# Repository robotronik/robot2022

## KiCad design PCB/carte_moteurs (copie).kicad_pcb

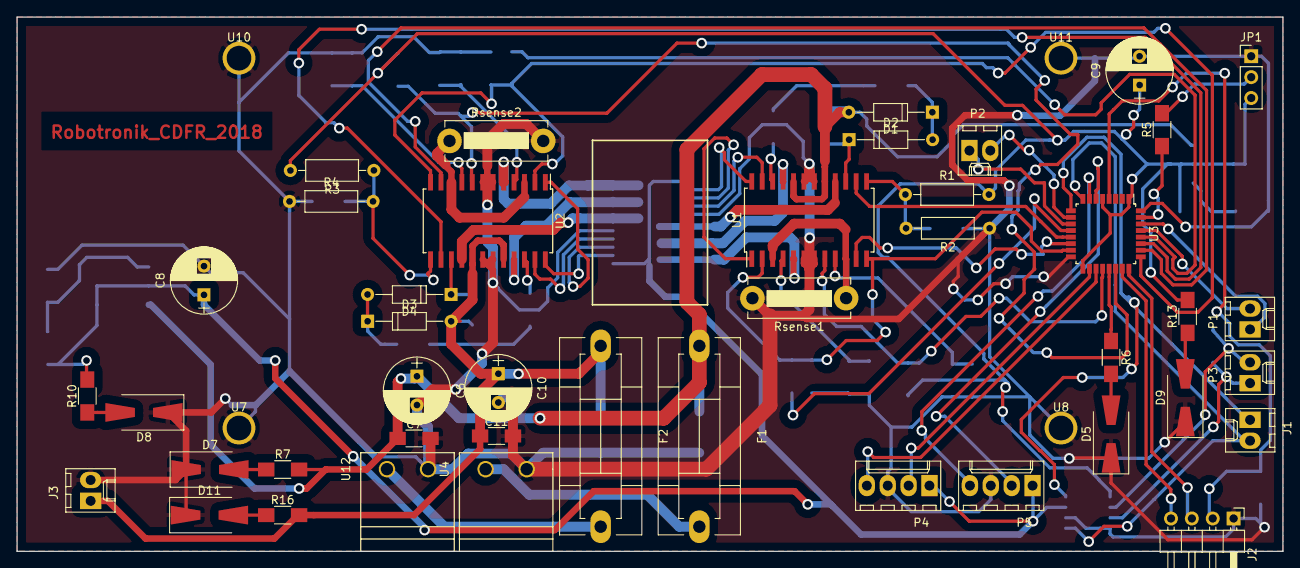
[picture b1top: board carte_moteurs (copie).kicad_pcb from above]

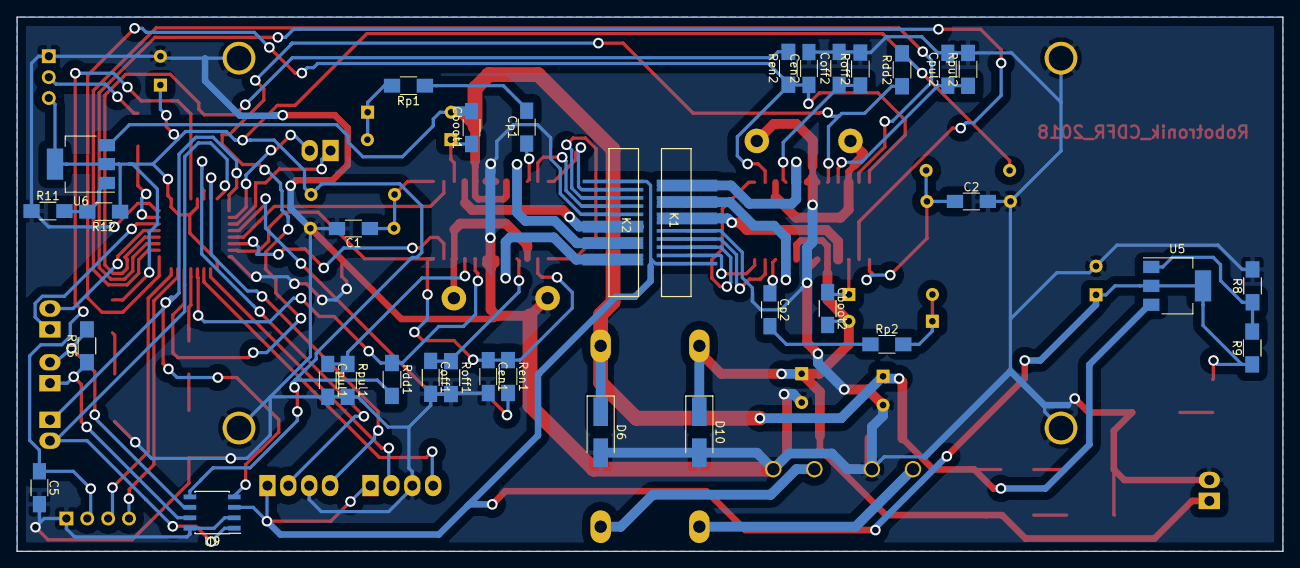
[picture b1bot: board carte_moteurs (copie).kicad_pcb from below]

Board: 2 copper layers, 154.0 x 65.0 mm, 82 parts (35 on the bottom side), 70 nets.

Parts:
C1, C2: C; C_1206_HandSoldering
C5, C7, C11: 100nC; C_1206_HandSoldering
C6, C10: 100uCP; CP_Radial_D8.0mm_P3.50mm
C8, C9: 10uC; CP_Radial_D8.0mm_P3.50mm
Cboot1, Cboot2: 220nC; C_1206_HandSoldering
Cen1, Cen2: 5,6nC; C_1206_HandSoldering
Coff1, Coff2: 1nC; C_1206_HandSoldering
Cp1, Cp2: 10nC; C_1206_HandSoldering
Cpul1, Cpul2: 10nC; C_1206_HandSoldering
D1, D2, D3, D4: 1N4148; D_DO-35_SOD27_P10.16mm_Horizontal
D5, D11: LED_ALT; D_SMA-SMB_Universal_Handsoldering
D6, D10: D_10A; D_SMA_Handsoldering
D7: LED_VCC; D_SMA-SMB_Universal_Handsoldering
D8: LED_5V; D_SMA-SMB_Universal_Handsoldering
D9: LED_3.3V; D_SMA-SMB_Universal_Handsoldering
F1, F2: Fuse; Fuseholder5x20_horiz_SemiClosed_Casing10x25mm
J1: CONN_SERIAL; Molex_KK-6410-02_02x2.54mm_Straight
J2: swdio; Pin_Header_Angled_1x04_Pitch2.54mm
J3: FAN; Molex_KK-6410-02_02x2.54mm_Straight
JP1: Jumper_NC_Dual; Pin_Header_Straight_1x03_Pitch2.54mm
K1, K2: Maxon-200142; Molex-52610-1133
P1: CONN_I2C; Molex_KK-6410-02_02x2.54mm_Straight
P2: CONN_FREE; Molex_KK-6410-02_02x2.54mm_Straight
P3: CONN_CAN; Molex_KK-6410-02_02x2.54mm_Straight
P4: encoder_2; Molex_KK-6410-04_04x2.54mm_Straight
P5: encoder_1; Molex_KK-6410-04_04x2.54mm_Straight
R1, R2, R3, R4: R; R_Axial_DIN0207_L6.3mm_D2.5mm_P10.16mm_Horizontal
R5, R9: 10kR; R_1206_HandSoldering
R6, R7, R10, R13, R15, R16: R; R_1206_HandSoldering
R8: 3.3kR; R_1206_HandSoldering
R11: 33kR; R_1206_HandSoldering
R12: 56kR; R_1206_HandSoldering
Rdd1, Rdd2: 1kR; R_1206_HandSoldering
Ren1, Ren2: 100kR; R_1206_HandSoldering
Roff1, Roff2: 33kR; R_1206_HandSoldering
Rp1, Rp2: 100R; R_1206_HandSoldering
Rpul1, Rpul2: 47kR; R_1206_HandSoldering
Rsense1, Rsense2: 0.03R; R_Bare_Metal_Element_L12.4mm_W4.8mm_P11.40mm
U1, U2: L6235D; SOIC-24W_7.5x15.4mm_Pitch1.27mm
U3: stm32f303k8t6; LQFP-32_7x7mm_Pitch0.8mm
U4, U12: B_Plug_5mm; B plug 5mm
U5, U6: LM317_SOT223; SOT-223-3Lead_TabPin2
U7, U8, U10, U11: Trou-3
U9: MCP2562; SOIC-8_3.9x4.9mm_Pitch1.27mm

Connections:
+3V3: C9.1, JP1.3, R1.2, R3.2, R12.1, R13.2, Rdd1.2, Rdd2.2, U3.1, U3.5, U3.17, U6.2, U9.5
+5V: C8.1, K1.11, K2.11, P4.1, P5.1, R9.1, R10.2, U5.2, U9.3
/encodeurs/Ch_A1: P5.2, U3.6
/encodeurs/Ch_A2: P4.2, U3.18
/encodeurs/Ch_B1: P5.4, U3.7
/encodeurs/Ch_B2: P4.4, U3.19
/motor_part/BRAKE_1: U1.14, U3.13
/motor_part/BRAKE_2: U2.14, U3.27
/motor_part/DIAG_1: Cen1.1, Ren1.1, U1.2, U1.12, U3.15
/motor_part/DIAG_2: Cen2.1, Ren2.1, U2.2, U2.12, U3.25
/motor_part/DIR_1: U1.11, U3.14
/motor_part/DIR_2: U2.11, U3.26
/motor_part/EN_1: Ren1.2, U3.12
/motor_part/EN_2: Ren2.2, U3.28
/motor_part/RCOFF1: Coff1.1, Roff1.1, U1.4
/motor_part/RCOFF2: Coff2.1, Roff2.1, U2.4
/motor_part/RCPULSE1: Cpul1.1, Rpul1.1, U1.9
/motor_part/RCPULSE2: Cpul2.1, Rpul2.1, U2.9
/motor_part/TACHO_1: Rdd1.1, U1.8, U3.20
/motor_part/TACHO_2: Rdd2.1, U2.8, U3.22
/motor_part/VBOOT1: Cboot1.1, D2.1, U1.15
/motor_part/VBOOT2: Cboot2.1, D4.1, U2.15
/motor_part/VCP1: Cp1.1, U1.22
/motor_part/VCP2: Cp2.1, U2.22
/motor_part/Vref1: C1.1, R1.1, R2.2, U1.13
/motor_part/Vref2: C2.1, R3.1, R4.2, U2.13
/uC/I2C_SCL: P1.2, U3.29
/uC/I2C_SDA: P1.1, U3.30
/uC/RX: J1.1, U3.9, U9.4
/uC/TX: J1.2, U3.8, U9.1
/uC/nrst: C5.1, J2.2, U3.4
/uC/swclk: J2.3, U3.24
/uC/swdio: J2.4, U3.23
GND: C1.2, C2.2, C5.2, C6.2, C7.2, C8.2, C9.2, C10.2, C11.2, Cen1.2, Cen2.2, Coff1.2, Coff2.2, Cpul1.2, Cpul2.2, D5.1, D6.2, D7.1, D8.1, D9.1, D10.2, D11.1, J2.1, J3.2, JP1.1, K1.7, K2.7, P4.3, P5.3, R2.1, R4.1, R8.2, R11.1, Roff1.2, Roff2.2, Rpul1.2, Rpul2.2, Rsense1.2, Rsense2.2, U1.6, U1.7, U1.18, U1.19, U2.6, U2.7, U2.18, U2.19, U3.16, U3.32, U4.2, U7.1, U8.1, U9.2, U9.8, U10.1, U11.1, U12.2
unnamed: Cp1.2, Rp1.1
unnamed: Cp2.2, Rp2.1
unnamed: D1.1, D2.2, Rp1.2
unnamed: D3.1, D4.2, Rp2.2
unnamed: D5.2, R6.2
unnamed: D7.2, R7.1
unnamed: D8.2, R10.1
unnamed: D9.2, R13.1
unnamed: D11.2, R16.1
unnamed: F1.2, U4.1
unnamed: F2.2, U12.1
unnamed: JP1.2, R5.2
unnamed: K1.1, K1.2, U1.5
unnamed: K1.3, K1.4, U1.21
unnamed: K1.5, K1.6, U1.16
unnamed: K1.8, U1.23
unnamed: K1.9, U1.1
unnamed: K1.10, U1.24
unnamed: K2.1, K2.2, U2.5
unnamed: K2.3, K2.4, U2.21
unnamed: K2.5, K2.6, U2.16
unnamed: K2.8, U2.23
unnamed: K2.9, U2.1
unnamed: K2.10, U2.24
unnamed: P2.1, U3.11
unnamed: P2.2, U3.10
unnamed: P3.1, R15.1, U9.7
unnamed: P3.2, R15.2, U9.6
unnamed: R5.1, U3.31
unnamed: R6.1, U3.21
unnamed: R8.1, R9.2, U5.1
unnamed: R11.2, R12.2, U6.1
unnamed: Rsense1.1, U1.3, U1.10
unnamed: Rsense2.1, U2.3, U2.10
VCC: C6.1, C7.1, Cboot1.2, D1.2, D6.1, F1.1, R7.2, U1.17, U1.20, U5.3, U6.3
VDD: C10.1, C11.1, Cboot2.2, D3.2, D10.1, F2.1, J3.1, R16.2, U2.17, U2.20

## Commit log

2022-11-10 Backup
